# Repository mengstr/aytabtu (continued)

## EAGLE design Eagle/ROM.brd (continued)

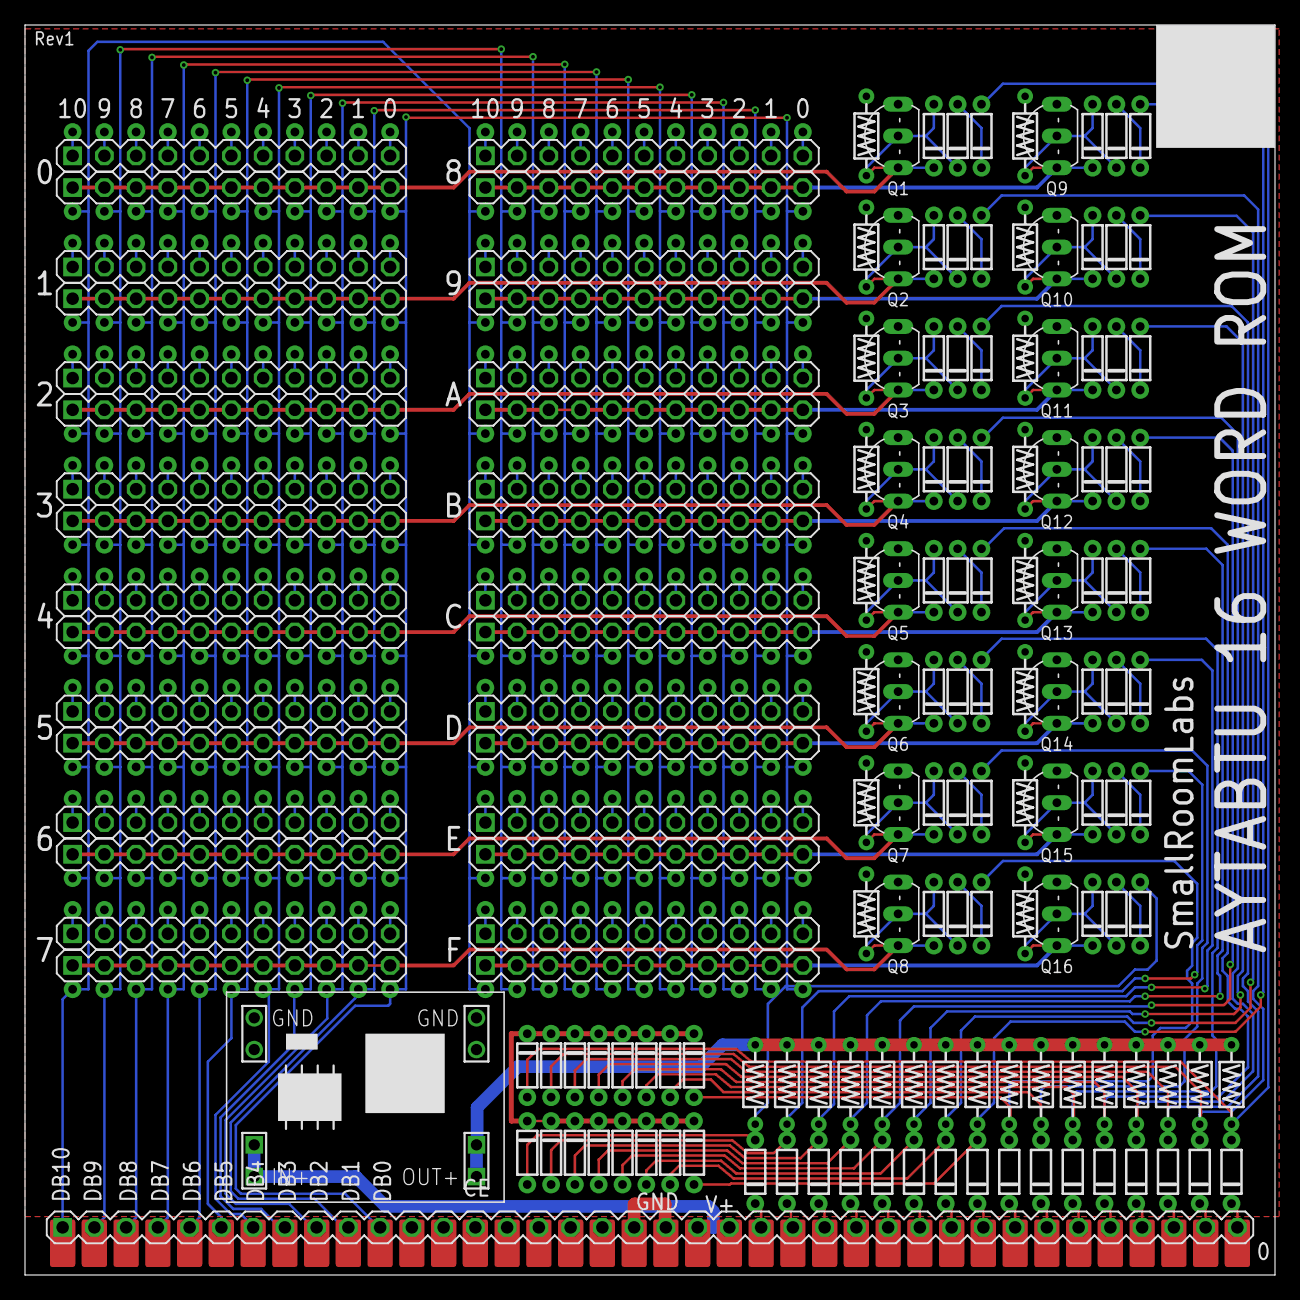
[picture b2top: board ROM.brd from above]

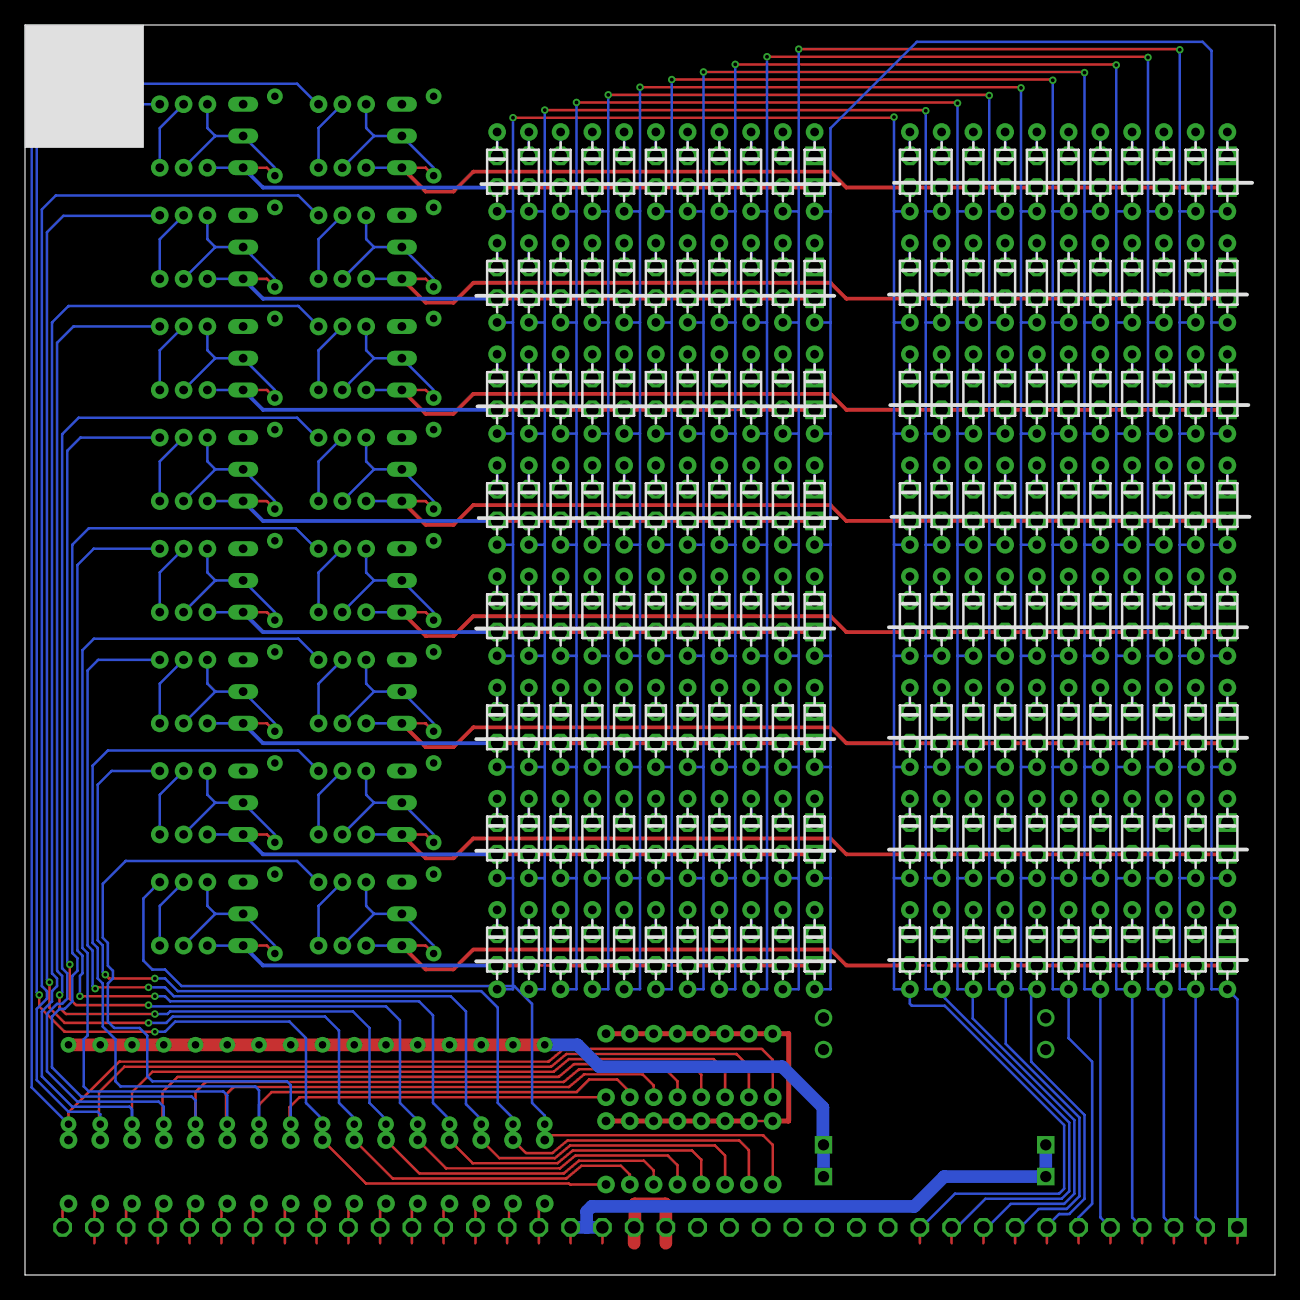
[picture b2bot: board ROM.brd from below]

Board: 2 copper layers, 100.0 x 100.0 mm, 338 parts (176 on the bottom side), 271 nets.

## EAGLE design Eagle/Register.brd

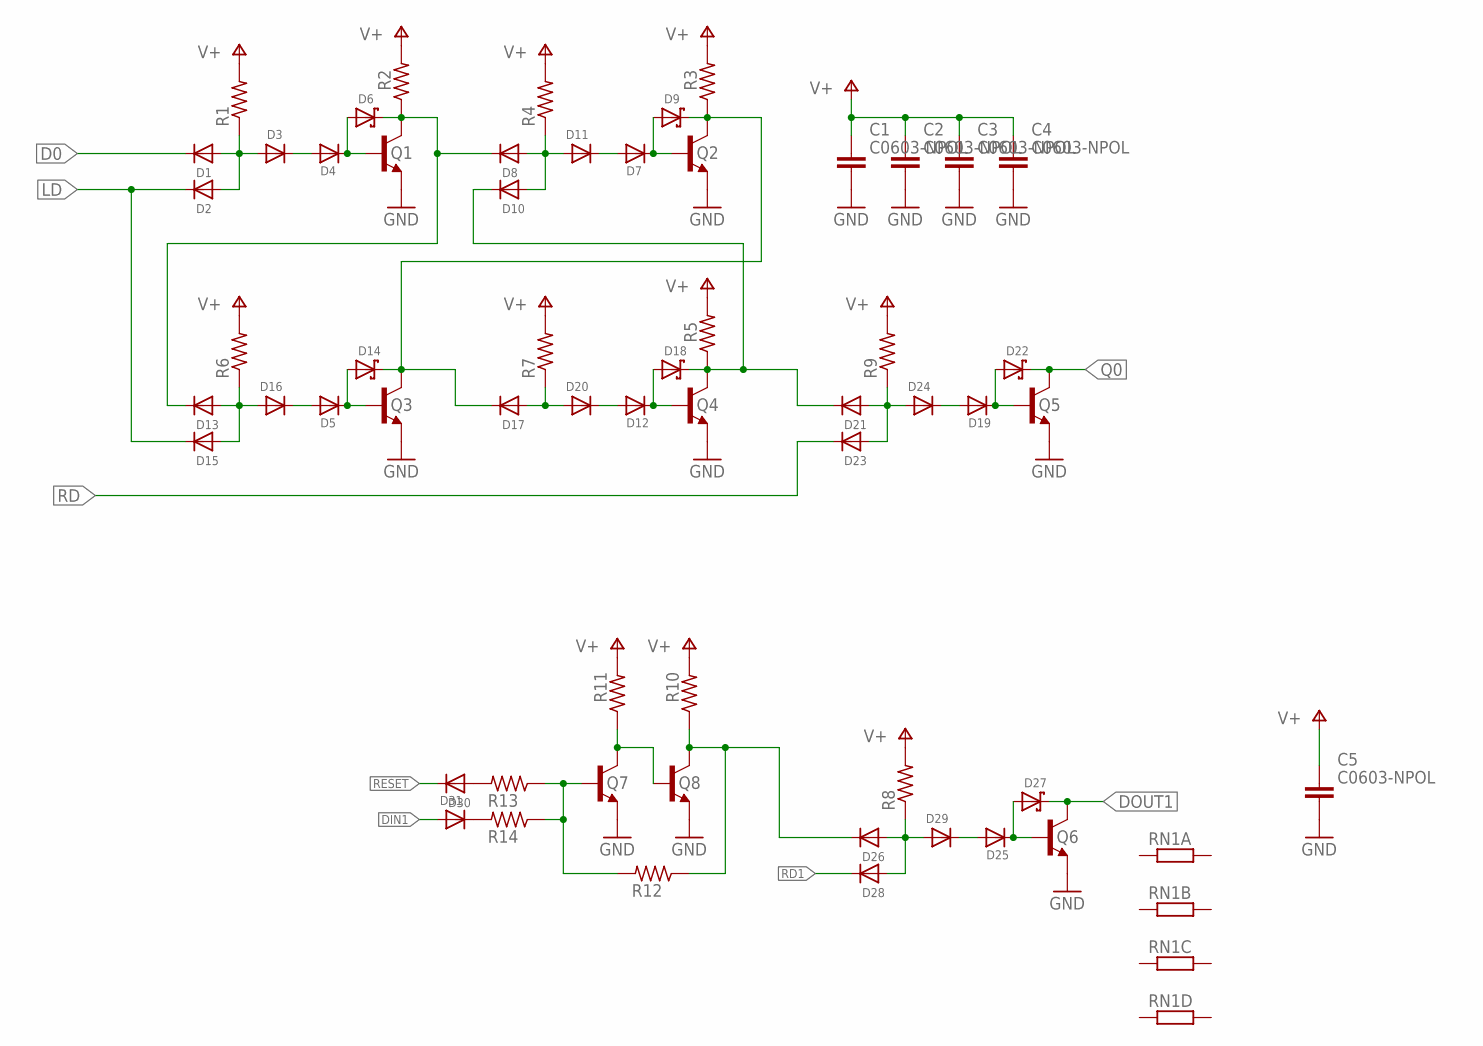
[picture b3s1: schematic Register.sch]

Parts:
C1, C2, C3, C4, C5: C0603-NPOL; C0603
D1, D2, D3, D4, D5, D7, D8, D10, D11, D12, D13, D15, D16, D17, D19, D20, D21, D23, D24, D25, D26, D28, D29, D30, D31: DIODE-SOD323; SOD323F
D6, D9, D14, D18, D22, D27: SCHOTTKYSOT323; SOT23
Q1, Q2, Q3, Q4, Q5, Q6, Q7, Q8: BC547-SOT23; SOT23
R1, R4, R6, R7, R8, R9: 470; R0805
R2, R3, R5, R10, R11, R12, R13, R14: 150; R0805
RN1: RESISTOR_ARRAY_4; RN8P-4R-CRA06S

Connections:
D0: D1.C
DIN1: D31.A
DOUT1: D27.3 (C), Q6.3 (C)
GND: C1.2, C2.2, C3.2, C4.2, C5.2, Q1.2 (E), Q2.2 (E), Q3.2 (E), Q4.2 (E), Q5.2 (E), Q6.2 (E), Q7.2 (E), Q8.2 (E)
LD: D2.C, D15.C
unnamed: D1.A, D2.A, D3.A, R1.1
unnamed: D3.C, D4.A
unnamed: D4.C, D6.1 (A), Q1.1 (B)
unnamed: D13.A, D15.A, D16.A, R6.1
unnamed: D8.A, D10.A, D11.A, R4.1
unnamed: D5.A, D16.C
unnamed: D7.A, D11.C
unnamed: D5.C, D14.1 (A), Q3.1 (B)
unnamed: D7.C, D9.1 (A), Q2.1 (B)
unnamed: D17.A, D20.A, R7.1
unnamed: D12.A, D20.C
unnamed: D12.C, D18.1 (A), Q4.1 (B)
unnamed: D21.A, D23.A, D24.A, R9.1
unnamed: D19.A, D24.C
unnamed: D19.C, D22.1 (A), Q5.1 (B)
unnamed: D26.C, Q8.3 (C), R10.1, R12.1
unnamed: D26.A, D28.A, D29.A, R8.1
unnamed: D25.A, D29.C
unnamed: D25.C, D27.1 (A), Q6.1 (B)
unnamed: Q7.3 (C), Q8.1 (B), R11.1
unnamed: Q7.1 (B), R12.2, R13.1, R14.1
unnamed: D30.A, R13.2
unnamed: D31.C, R14.2
unnamed: D10.C, D18.3 (C), D21.C, Q4.3 (C), R5.1
unnamed: D9.3 (C), D14.3 (C), D17.C, Q2.3 (C), Q3.3 (C), R3.1
unnamed: D6.3 (C), D8.C, D13.C, Q1.3 (C), R2.1
Q0: D22.3 (C), Q5.3 (C)
RD: D23.C
RD1: D28.C
RESET: D30.C
V+: C1.1, C2.1, C3.1, C4.1, C5.1, R1.2, R2.2, R3.2, R4.2, R5.2, R6.2, R7.2, R8.2, R9.2, R10.2, R11.2

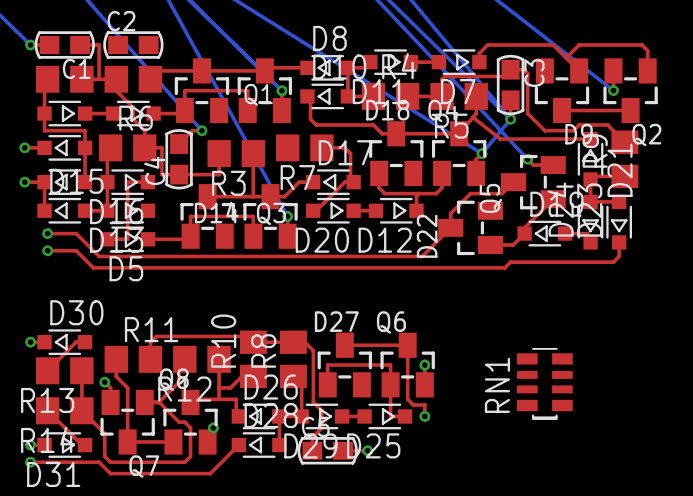
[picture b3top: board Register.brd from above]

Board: 2 copper layers, 59 parts (0 on the bottom side), 31 nets.

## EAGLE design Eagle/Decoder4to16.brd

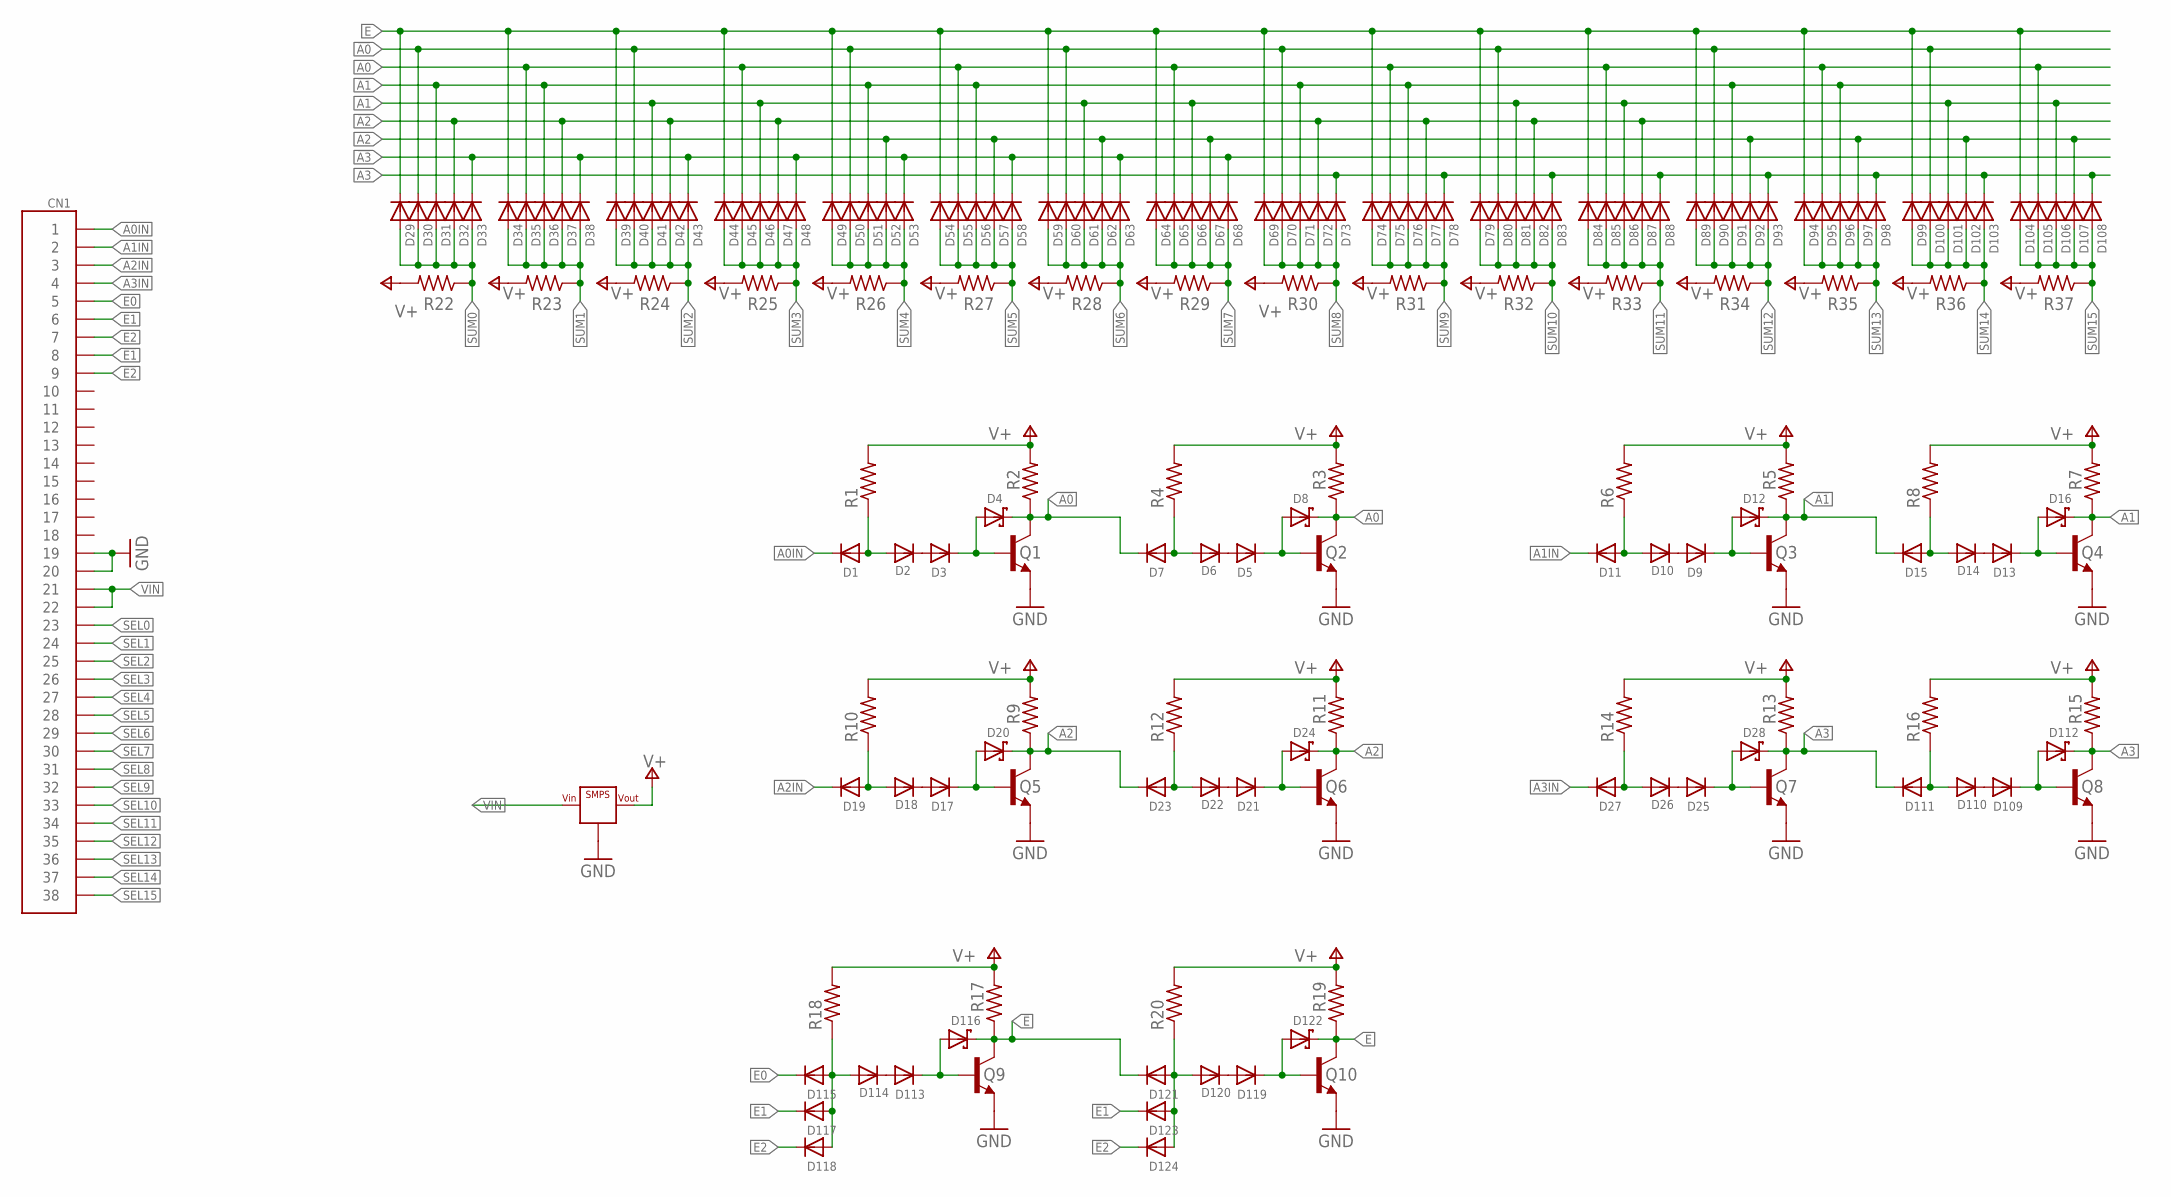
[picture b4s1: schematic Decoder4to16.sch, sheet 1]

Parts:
CN1: HD38-HP; HD38-HOLEPAD
D1, D2, D3, D5, D6, D7, D9, D10, D11, D13, D14, D15, D17, D18, D19, D21, D22, D23, D25, D26, D27, D29, D30, D31, D32, D33, D34, D35, D36, D37, D38, D39, D40, D41, D42, D43, D44, D45, D46, D47, D48, D49, D50, D51, D52, D53, D54, D55, D56, D57, D58, D59, D60, D61, D62, D63, D64, D65, D66, D67, D68, D69, D70, D71, D72, D73, D74, D75, D76, D77, D78, D79, D80, D81, D82, D83, D84, D85, D86, D87, D88, D89, D90, D91, D92, D93, D94, D95, D96, D97, D98, D99, D100, D101, D102, D103, D104, D105, D106, D107, D108, D109, D110, D111, D113, D114, D115, D117, D118, D119, D120, D121, D123, D124: DIODE-SOD323; SOD323F
D4, D8, D12, D16, D20, D24, D28, D112, D116, D122: SCHOTTKYSOT323; SOT23
Q1, Q2, Q3, Q4, Q5, Q6, Q7, Q8, Q9, Q10: BC547-SOT23; SOT23
R1, R4, R6, R8, R10, R12, R14, R16, R18, R20: 470; R0805
R2, R3, R5, R7, R9, R11, R13, R15, R17, R19: 150; R0805
R22, R23, R24, R25, R26, R27, R28, R29, R30, R31, R32, R33, R34, R35, R36, R37: R-0805; R0805
VR1: SMPS; BUCK1722

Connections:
!A0: D4.3 (C), D7.C, D30.C, D40.C, D50.C, D60.C, D70.C, D80.C, D90.C, D100.C, Q1.3 (C), R2.1
!A1: D12.3 (C), D15.C, D31.C, D36.C, D51.C, D56.C, D71.C, D76.C, D91.C, D96.C, Q3.3 (C), R5.1
!A2: D20.3 (C), D23.C, D32.C, D37.C, D42.C, D47.C, D72.C, D77.C, D82.C, D87.C, Q5.3 (C), R9.1
!A3: D28.3 (C), D33.C, D38.C, D43.C, D48.C, D53.C, D58.C, D63.C, D68.C, D111.C, Q7.3 (C), R13.1
!E: D116.3 (C), D121.C, Q9.3 (C), R17.1
!E1: CN1.P8@1 (8), CN1.P8@2 (8), D123.C
!E2: CN1.P9@1 (9), CN1.P9@2 (9), D124.C
A0: D8.3 (C), D35.C, D45.C, D55.C, D65.C, D75.C, D85.C, D95.C, D105.C, Q2.3 (C), R3.1
A0IN: CN1.P1@1 (1), CN1.P1@2 (1), D1.C
A1: D16.3 (C), D41.C, D46.C, D61.C, D66.C, D81.C, D86.C, D101.C, D106.C, Q4.3 (C), R7.1
A1IN: CN1.P2@1 (2), CN1.P2@2 (2), D11.C
A2: D24.3 (C), D52.C, D57.C, D62.C, D67.C, D92.C, D97.C, D102.C, D107.C, Q6.3 (C), R11.1
A2IN: CN1.P3@1 (3), CN1.P3@2 (3), D19.C
A3: D73.C, D78.C, D83.C, D88.C, D93.C, D98.C, D103.C, D108.C, D112.3 (C), Q8.3 (C), R15.1
A3IN: CN1.P4@1 (4), CN1.P4@2 (4), D27.C
E: D29.C, D34.C, D39.C, D44.C, D49.C, D54.C, D59.C, D64.C, D69.C, D74.C, D79.C, D84.C, D89.C, D94.C, D99.C, D104.C, D122.3 (C), Q10.3 (C), R19.1
E0: CN1.P5@1 (5), CN1.P5@2 (5), D115.C
E1: CN1.P6@1 (6), CN1.P6@2 (6), D117.C
E2: CN1.P7@1 (7), CN1.P7@2 (7), D118.C
GND: CN1.P19@1 (19), CN1.P19@2 (19), CN1.P20@1 (20), CN1.P20@2 (20), Q1.2 (E), Q2.2 (E), Q3.2 (E), Q4.2 (E), Q5.2 (E), Q6.2 (E), Q7.2 (E), Q8.2 (E), Q9.2 (E), Q10.2 (E), VR1.GND@1 (GND), VR1.GND@2 (GND), VR1.GND@3 (GND), VR1.GND@4 (GND); also elsewhere on the board
unnamed: D1.A, D2.A, R1.1
unnamed: D3.C, D4.1 (A), Q1.1 (B)
unnamed: D2.C, D3.A
unnamed: D5.C, D8.1 (A), Q2.1 (B)
unnamed: D5.A, D6.C
unnamed: D6.A, D7.A, R4.1
unnamed: D9.C, D12.1 (A), Q3.1 (B)
unnamed: D9.A, D10.C
unnamed: D10.A, D11.A, R6.1
unnamed: D13.C, D16.1 (A), Q4.1 (B)
unnamed: D13.A, D14.C
unnamed: D14.A, D15.A, R8.1
unnamed: D17.C, D20.1 (A), Q5.1 (B)
unnamed: D17.A, D18.C
unnamed: D18.A, D19.A, R10.1
unnamed: D21.C, D24.1 (A), Q6.1 (B)
unnamed: D21.A, D22.C
unnamed: D22.A, D23.A, R12.1
unnamed: D25.C, D28.1 (A), Q7.1 (B)
unnamed: D25.A, D26.C
unnamed: D26.A, D27.A, R14.1
unnamed: D109.C, D112.1 (A), Q8.1 (B)
unnamed: D109.A, D110.C
unnamed: D110.A, D111.A, R16.1
unnamed: D113.C, D116.1 (A), Q9.1 (B)
unnamed: D113.A, D114.C
unnamed: D119.C, D122.1 (A), Q10.1 (B)
unnamed: D119.A, D120.C
unnamed: D120.A, D121.A, D123.A, D124.A, R20.1
unnamed: D114.A, D115.A, D117.A, D118.A, R18.1
SEL0: CN1.P23@1 (23), CN1.P23@2 (23); also elsewhere on the board
SEL1: CN1.P24@1 (24), CN1.P24@2 (24); also elsewhere on the board
SEL2: CN1.P25@1 (25), CN1.P25@2 (25); also elsewhere on the board
SEL3: CN1.P26@1 (26), CN1.P26@2 (26); also elsewhere on the board
SEL4: CN1.P27@1 (27), CN1.P27@2 (27); also elsewhere on the board
SEL5: CN1.P28@1 (28), CN1.P28@2 (28); also elsewhere on the board
SEL6: CN1.P29@1 (29), CN1.P29@2 (29); also elsewhere on the board
SEL7: CN1.P30@1 (30), CN1.P30@2 (30); also elsewhere on the board
SEL8: CN1.P31@1 (31), CN1.P31@2 (31); also elsewhere on the board
SEL9: CN1.P32@1 (32), CN1.P32@2 (32); also elsewhere on the board
SEL10: CN1.P33@1 (33), CN1.P33@2 (33); also elsewhere on the board
SEL11: CN1.P34@1 (34), CN1.P34@2 (34); also elsewhere on the board
SEL12: CN1.P35@1 (35), CN1.P35@2 (35); also elsewhere on the board
SEL13: CN1.P36@1 (36), CN1.P36@2 (36); also elsewhere on the board
SEL14: CN1.P37@1 (37), CN1.P37@2 (37); also elsewhere on the board
SEL15: CN1.P38@1 (38), CN1.P38@2 (38); also elsewhere on the board
SUM0: D29.A, D30.A, D31.A, D32.A, D33.A, R22.1; also elsewhere on the board
SUM1: D34.A, D35.A, D36.A, D37.A, D38.A, R23.1; also elsewhere on the board
SUM2: D39.A, D40.A, D41.A, D42.A, D43.A, R24.1; also elsewhere on the board
SUM3: D44.A, D45.A, D46.A, D47.A, D48.A, R25.1; also elsewhere on the board
SUM4: D49.A, D50.A, D51.A, D52.A, D53.A, R26.1; also elsewhere on the board
SUM5: D54.A, D55.A, D56.A, D57.A, D58.A, R27.1; also elsewhere on the board
SUM6: D59.A, D60.A, D61.A, D62.A, D63.A, R28.1; also elsewhere on the board
SUM7: D64.A, D65.A, D66.A, D67.A, D68.A, R29.1; also elsewhere on the board
SUM8: D69.A, D70.A, D71.A, D72.A, D73.A, R30.1; also elsewhere on the board
SUM9: D74.A, D75.A, D76.A, D77.A, D78.A, R31.1; also elsewhere on the board
SUM10: D79.A, D80.A, D81.A, D82.A, D83.A, R32.1; also elsewhere on the board
SUM11: D84.A, D85.A, D86.A, D87.A, D88.A, R33.1; also elsewhere on the board
SUM12: D89.A, D90.A, D91.A, D92.A, D93.A, R34.1; also elsewhere on the board
SUM13: D94.A, D95.A, D96.A, D97.A, D98.A, R35.1; also elsewhere on the board
SUM14: D99.A, D100.A, D101.A, D102.A, D103.A, R36.1; also elsewhere on the board
SUM15: D104.A, D105.A, D106.A, D107.A, D108.A, R37.1; also elsewhere on the board
V+: R1.2, R2.2, R3.2, R4.2, R5.2, R6.2, R7.2, R8.2, R9.2, R10.2, R11.2, R12.2, R13.2, R14.2, R15.2, R16.2, R17.2, R18.2, R19.2, R20.2, R22.2, R23.2, R24.2, R25.2, R26.2, R27.2, R28.2, R29.2, R30.2, R31.2, R32.2, R33.2, R34.2, R35.2, R36.2, R37.2, VR1.OUT@1 (VOUT), VR1.OUT@2 (VOUT); also elsewhere on the board
VIN: CN1.P21@1 (21), CN1.P21@2 (21), CN1.P22@1 (22), CN1.P22@2 (22), VR1.IN@1 (VIN), VR1.IN@2 (VIN)

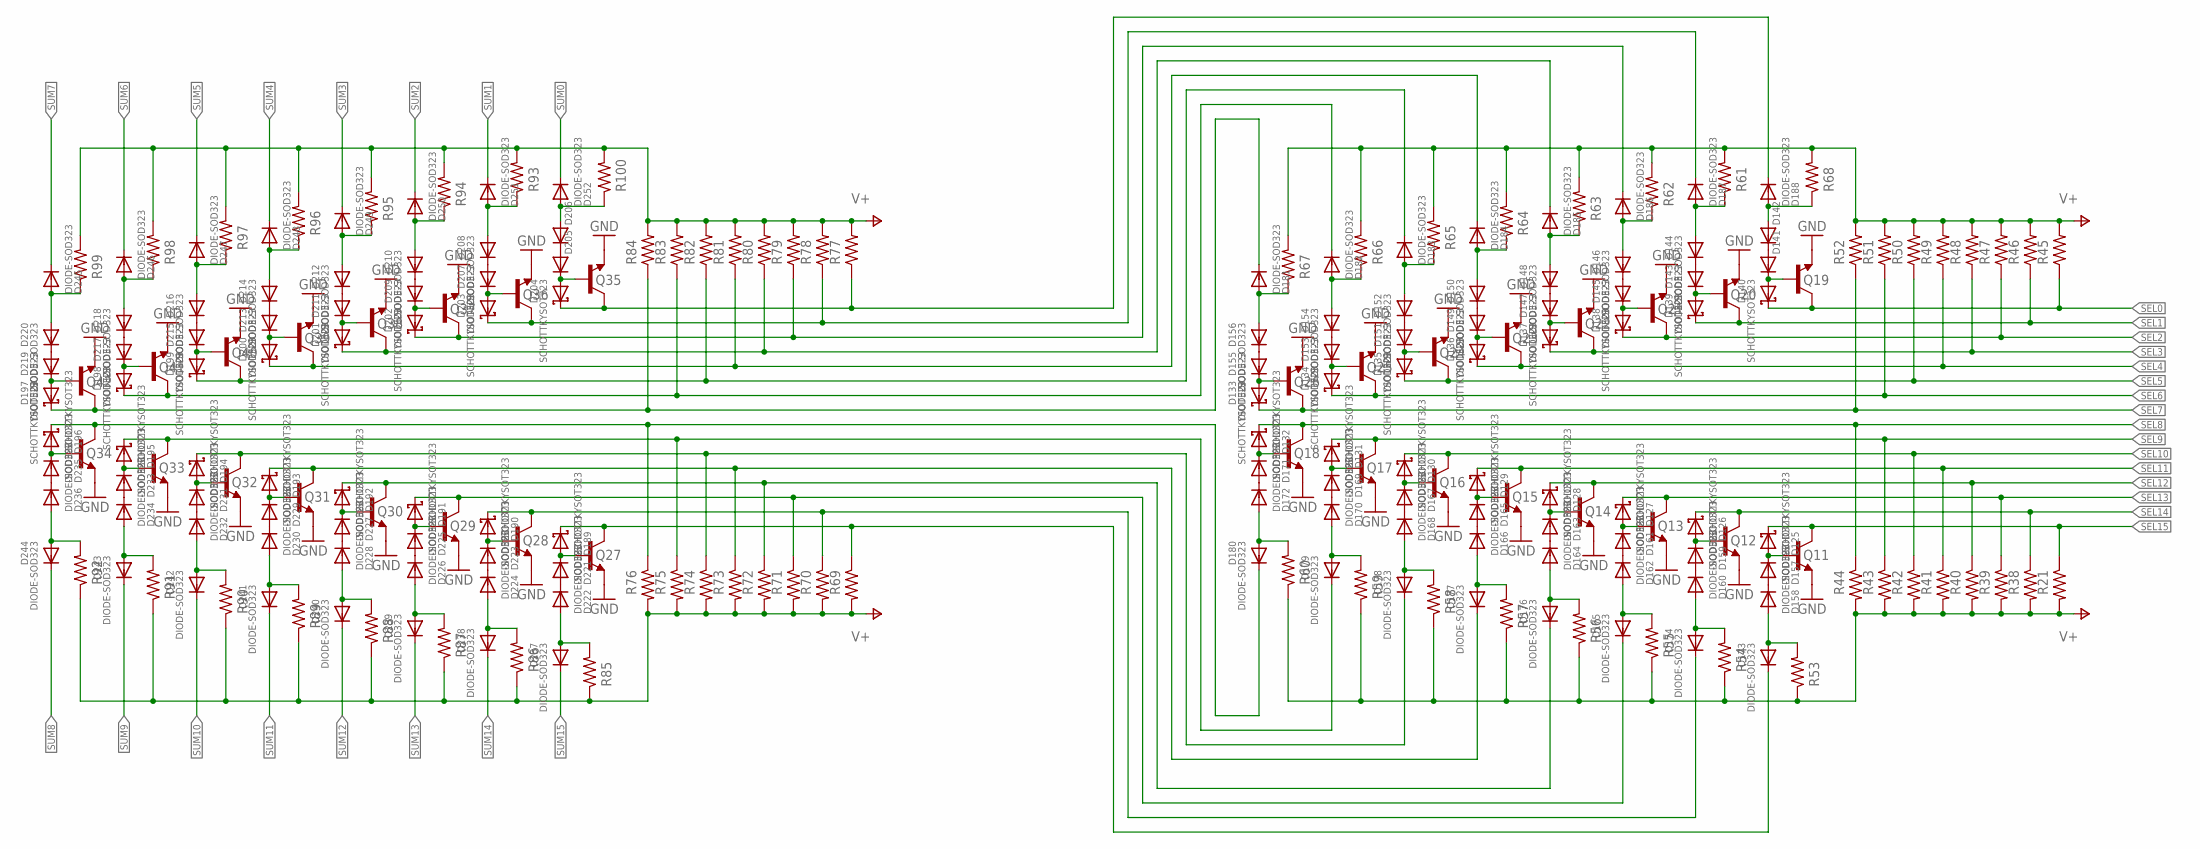
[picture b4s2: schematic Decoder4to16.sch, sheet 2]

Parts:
D125, D126, D127, D128, D129, D130, D131, D132, D133, D134, D135, D136, D137, D138, D139, D140, D189, D190, D191, D192, D193, D194, D195, D196, D197, D198, D199, D200, D201, D202, D203, D204: SCHOTTKYSOT323; SOT23
D141, D142, D143, D144, D145, D146, D147, D148, D149, D150, D151, D152, D153, D154, D155, D156, D157, D158, D159, D160, D161, D162, D163, D164, D165, D166, D167, D168, D169, D170, D171, D172, D173, D174, D175, D176, D177, D178, D179, D180, D181, D182, D183, D184, D185, D186, D187, D188, D205, D206, D207, D208, D209, D210, D211, D212, D213, D214, D215, D216, D217, D218, D219, D220, D221, D222, D223, D224, D225, D226, D227, D228, D229, D230, D231, D232, D233, D234, D235, D236, D237, D238, D239, D240, D241, D242, D243, D244, D245, D246, D247, D248, D249, D250, D251, D252: DIODE-SOD323; SOD323F
Q11, Q12, Q13, Q14, Q15, Q16, Q17, Q18, Q19, Q20, Q21, Q22, Q23, Q24, Q25, Q26, Q27, Q28, Q29, Q30, Q31, Q32, Q33, Q34, Q35, Q36, Q37, Q38, Q39, Q40, Q41, Q42: BC547-SOT23; SOT23
R21, R38, R39, R40, R41, R42, R43, R44, R45, R46, R47, R48, R49, R50, R51, R52, R53, R54, R55, R56, R57, R58, R59, R60, R61, R62, R63, R64, R65, R66, R67, R68, R69, R70, R71, R72, R73, R74, R75, R76, R77, R78, R79, R80, R81, R82, R83, R84, R85, R86, R87, R88, R89, R90, R91, R92, R93, R94, R95, R96, R97, R98, R99, R100: R-0805; R0805

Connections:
GND: Q11.2 (E), Q12.2 (E), Q13.2 (E), Q14.2 (E), Q15.2 (E), Q16.2 (E), Q17.2 (E), Q18.2 (E), Q19.2 (E), Q20.2 (E), Q21.2 (E), Q22.2 (E), Q23.2 (E), Q24.2 (E), Q25.2 (E), Q26.2 (E), Q27.2 (E), Q28.2 (E), Q29.2 (E), Q30.2 (E), Q31.2 (E), Q32.2 (E), Q33.2 (E), Q34.2 (E), Q35.2 (E), Q36.2 (E), Q37.2 (E), Q38.2 (E), Q39.2 (E), Q40.2 (E), Q41.2 (E), Q42.2 (E); also elsewhere on the board
unnamed: D125.1 (A), D157.C, Q11.1 (B)
unnamed: D126.1 (A), D159.C, Q12.1 (B)
unnamed: D127.1 (A), D161.C, Q13.1 (B)
unnamed: D128.1 (A), D163.C, Q14.1 (B)
unnamed: D129.1 (A), D165.C, Q15.1 (B)
unnamed: D130.1 (A), D167.C, Q16.1 (B)
unnamed: D131.1 (A), D169.C, Q17.1 (B)
unnamed: D132.1 (A), D171.C, Q18.1 (B)
unnamed: D140.1 (A), D141.C, Q19.1 (B)
unnamed: D139.1 (A), D143.C, Q20.1 (B)
unnamed: D138.1 (A), D145.C, Q21.1 (B)
unnamed: D137.1 (A), D147.C, Q22.1 (B)
unnamed: D136.1 (A), D149.C, Q23.1 (B)
unnamed: D135.1 (A), D151.C, Q24.1 (B)
unnamed: D134.1 (A), D153.C, Q25.1 (B)
unnamed: D133.1 (A), D155.C, Q26.1 (B)
unnamed: D141.A, D142.C
unnamed: D143.A, D144.C
unnamed: D145.A, D146.C
unnamed: D147.A, D148.C
unnamed: D149.A, D150.C
unnamed: D151.A, D152.C
unnamed: D153.A, D154.C
unnamed: D155.A, D156.C
unnamed: D157.A, D158.C
unnamed: D159.A, D160.C
unnamed: D161.A, D162.C
unnamed: D163.A, D164.C
unnamed: D165.A, D166.C
unnamed: D167.A, D168.C
unnamed: D169.A, D170.C
unnamed: D171.A, D172.C
unnamed: D158.A, D173.A, R53.2
unnamed: D160.A, D174.A, R54.2
unnamed: D162.A, D175.A, R55.2
unnamed: D164.A, D176.A, R56.2
unnamed: D166.A, D177.A, R57.2
unnamed: D168.A, D178.A, R58.2
unnamed: D170.A, D179.A, R59.2
unnamed: D172.A, D180.A, R60.2
unnamed: D156.A, D181.A, R67.1
unnamed: D154.A, D182.A, R66.1
unnamed: D152.A, D183.A, R65.1
unnamed: D150.A, D184.A, R64.1
unnamed: D148.A, D185.A, R63.1
unnamed: D146.A, D186.A, R62.1
unnamed: D144.A, D187.A, R61.1
unnamed: D142.A, D188.A, R68.1
unnamed: D189.1 (A), D221.C, Q27.1 (B)
unnamed: D190.1 (A), D223.C, Q28.1 (B)
unnamed: D191.1 (A), D225.C, Q29.1 (B)
unnamed: D192.1 (A), D227.C, Q30.1 (B)
unnamed: D193.1 (A), D229.C, Q31.1 (B)
unnamed: D194.1 (A), D231.C, Q32.1 (B)
unnamed: D195.1 (A), D233.C, Q33.1 (B)
unnamed: D196.1 (A), D235.C, Q34.1 (B)
unnamed: D204.1 (A), D205.C, Q35.1 (B)
unnamed: D203.1 (A), D207.C, Q36.1 (B)
unnamed: D202.1 (A), D209.C, Q37.1 (B)
unnamed: D201.1 (A), D211.C, Q38.1 (B)
unnamed: D200.1 (A), D213.C, Q39.1 (B)
unnamed: D199.1 (A), D215.C, Q40.1 (B)
unnamed: D198.1 (A), D217.C, Q41.1 (B)
unnamed: D197.1 (A), D219.C, Q42.1 (B)
unnamed: D205.A, D206.C
unnamed: D207.A, D208.C
unnamed: D209.A, D210.C
unnamed: D211.A, D212.C
unnamed: D213.A, D214.C
unnamed: D215.A, D216.C
unnamed: D217.A, D218.C
unnamed: D219.A, D220.C
unnamed: D221.A, D222.C
unnamed: D223.A, D224.C
unnamed: D225.A, D226.C
unnamed: D227.A, D228.C
unnamed: D229.A, D230.C
unnamed: D231.A, D232.C
unnamed: D233.A, D234.C
unnamed: D235.A, D236.C
unnamed: D222.A, D237.A, R85.2
unnamed: D224.A, D238.A, R86.2
unnamed: D226.A, D239.A, R87.2
unnamed: D228.A, D240.A, R88.2
unnamed: D230.A, D241.A, R89.2
unnamed: D232.A, D242.A, R90.2
unnamed: D234.A, D243.A, R91.2
unnamed: D236.A, D244.A, R92.2
unnamed: D220.A, D245.A, R99.1
unnamed: D218.A, D246.A, R98.1
unnamed: D216.A, D247.A, R97.1
unnamed: D214.A, D248.A, R96.1
unnamed: D212.A, D249.A, R95.1
unnamed: D210.A, D250.A, R94.1
unnamed: D208.A, D251.A, R93.1
unnamed: D206.A, D252.A, R100.1
SEL0: D140.3 (C), Q19.3 (C), R45.1; also elsewhere on the board
SEL1: D139.3 (C), Q20.3 (C), R46.1; also elsewhere on the board
SEL2: D138.3 (C), Q21.3 (C), R47.1; also elsewhere on the board
SEL3: D137.3 (C), Q22.3 (C), R48.1; also elsewhere on the board
SEL4: D136.3 (C), Q23.3 (C), R49.1; also elsewhere on the board
SEL5: D135.3 (C), Q24.3 (C), R50.1; also elsewhere on the board
SEL6: D134.3 (C), Q25.3 (C), R51.1; also elsewhere on the board
SEL7: D133.3 (C), Q26.3 (C), R52.1; also elsewhere on the board
SEL8: D132.3 (C), Q18.3 (C), R44.1; also elsewhere on the board
SEL9: D131.3 (C), Q17.3 (C), R43.1; also elsewhere on the board
SEL10: D130.3 (C), Q16.3 (C), R42.1; also elsewhere on the board
SEL11: D129.3 (C), Q15.3 (C), R41.1; also elsewhere on the board
SEL12: D128.3 (C), Q14.3 (C), R40.1; also elsewhere on the board
SEL13: D127.3 (C), Q13.3 (C), R39.1; also elsewhere on the board
SEL14: D126.3 (C), Q12.3 (C), R38.1; also elsewhere on the board
SEL15: D125.3 (C), Q11.3 (C), R21.1; also elsewhere on the board
SUM0: D252.C; also elsewhere on the board
SUM1: D251.C; also elsewhere on the board
SUM2: D250.C; also elsewhere on the board
SUM3: D249.C; also elsewhere on the board
SUM4: D248.C; also elsewhere on the board
SUM5: D247.C; also elsewhere on the board
SUM6: D246.C; also elsewhere on the board
SUM7: D245.C; also elsewhere on the board
SUM8: D244.C; also elsewhere on the board
SUM9: D243.C; also elsewhere on the board
SUM10: D242.C; also elsewhere on the board
SUM11: D241.C; also elsewhere on the board
SUM12: D240.C; also elsewhere on the board
SUM13: D239.C; also elsewhere on the board
SUM14: D238.C; also elsewhere on the board
SUM15: D237.C; also elsewhere on the board
V+: R21.2, R38.2, R39.2, R40.2, R41.2, R42.2, R43.2, R44.2, R45.2, R46.2, R47.2, R48.2, R49.2, R50.2, R51.2, R52.2, R53.1, R54.1, R55.1, R56.1, R57.1, R58.1, R59.1, R60.1, R61.2, R62.2, R63.2, R64.2, R65.2, R66.2, R67.2, R68.2, R69.2, R70.2, R71.2, R72.2, R73.2, R74.2, R75.2, R76.2, R77.2, R78.2, R79.2, R80.2, R81.2, R82.2, R83.2, R84.2, R85.1, R86.1, R87.1, R88.1, R89.1, R90.1, R91.1, R92.1, R93.2, R94.2, R95.2, R96.2, R97.2, R98.2, R99.2, R100.2; also elsewhere on the board
Z0: D188.C, D204.3 (C), Q35.3 (C), R77.1
Z1: D187.C, D203.3 (C), Q36.3 (C), R78.1
Z2: D186.C, D202.3 (C), Q37.3 (C), R79.1
Z3: D185.C, D201.3 (C), Q38.3 (C), R80.1
Z4: D184.C, D200.3 (C), Q39.3 (C), R81.1
Z5: D183.C, D199.3 (C), Q40.3 (C), R82.1
Z6: D182.C, D198.3 (C), Q41.3 (C), R83.1
Z7: D181.C, D197.3 (C), Q42.3 (C), R84.1
Z8: D180.C, D196.3 (C), Q34.3 (C), R76.1
Z9: D179.C, D195.3 (C), Q33.3 (C), R75.1
Z10: D178.C, D194.3 (C), Q32.3 (C), R74.1
Z11: D177.C, D193.3 (C), Q31.3 (C), R73.1
Z12: D176.C, D192.3 (C), Q30.3 (C), R72.1
Z13: D175.C, D191.3 (C), Q29.3 (C), R71.1
Z14: D174.C, D190.3 (C), Q28.3 (C), R70.1
Z15: D173.C, D189.3 (C), Q27.3 (C), R69.1

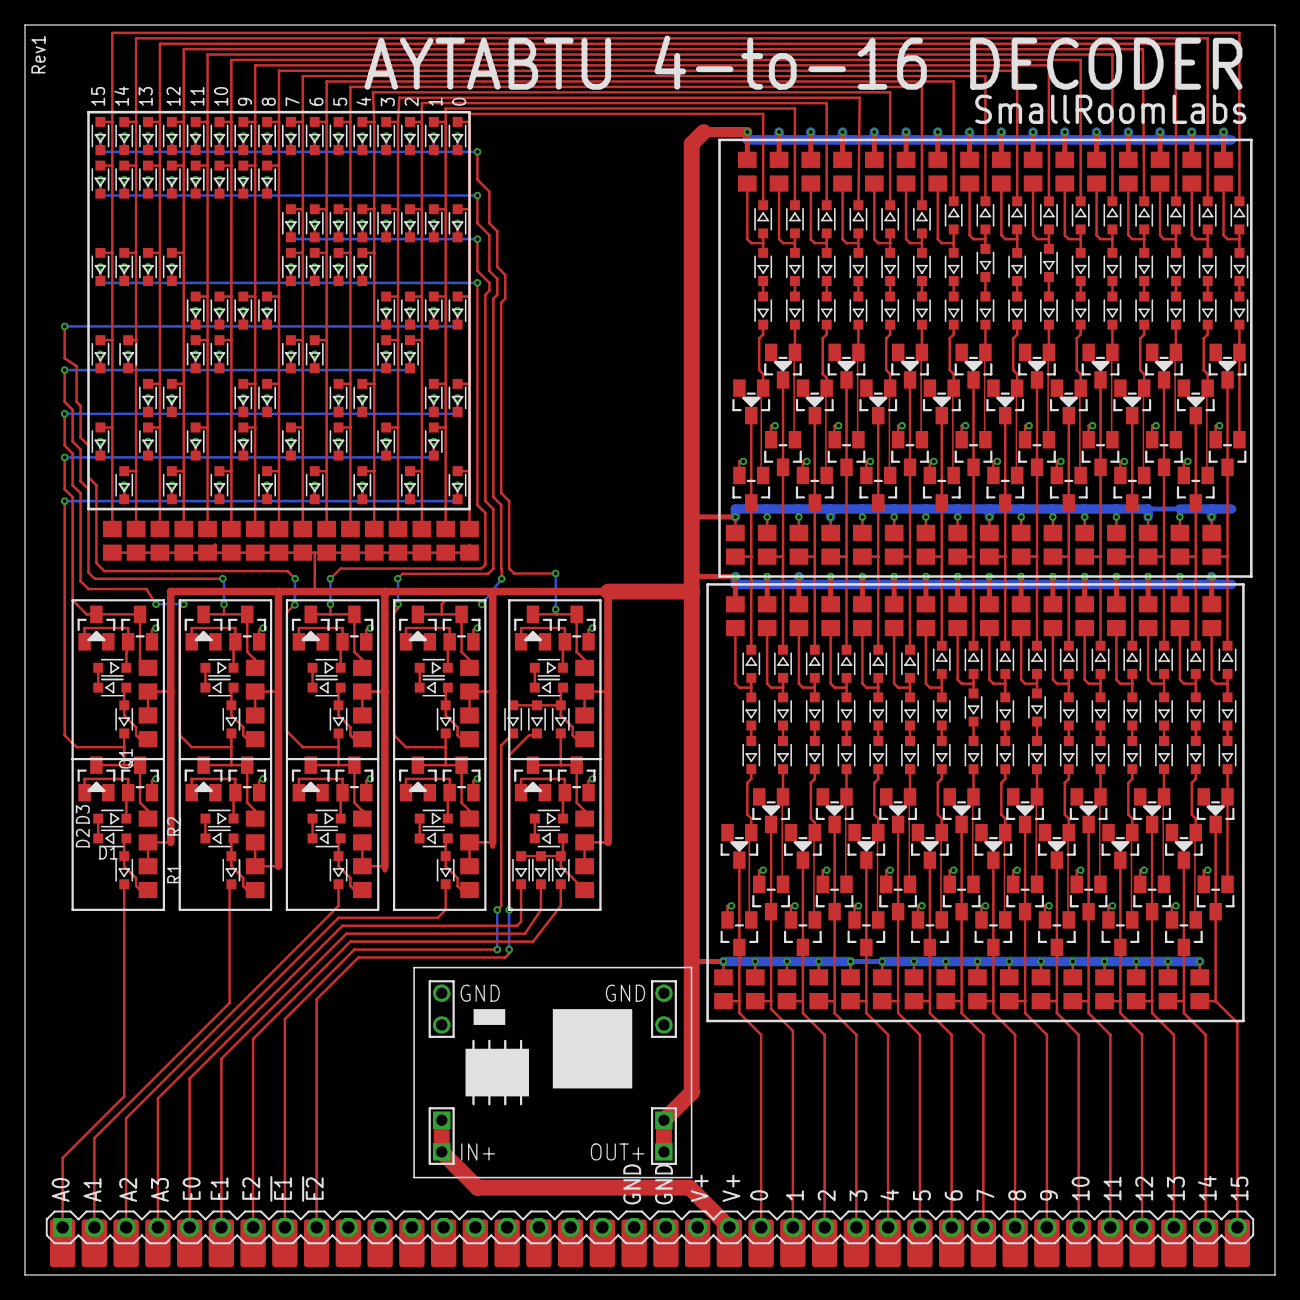
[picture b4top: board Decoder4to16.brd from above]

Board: 2 copper layers, 100.0 x 100.0 mm, 396 parts (0 on the bottom side), 196 nets.

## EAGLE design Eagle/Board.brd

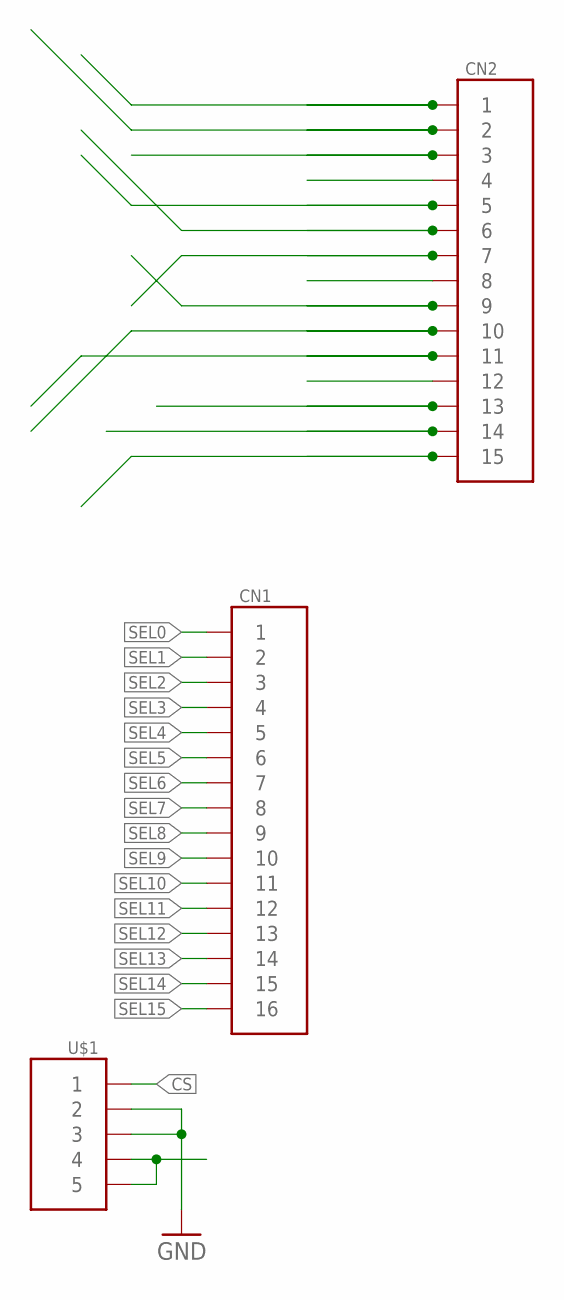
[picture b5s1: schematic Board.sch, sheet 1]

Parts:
CN1: HD16
CN2: HD15
U$1: HD5CN; HD5

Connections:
CS: U$1.P$1 (1)
GND: U$1.P$2 (2), U$1.P$3 (3); also elsewhere on the board
unnamed: U$1.P$4 (4), U$1.P$5 (5)
OUT0: CN2.P$1 (1)
OUT1: CN2.P$2 (2)
OUT2: CN2.P$3 (3)
OUT3: CN2.P$4 (4)
OUT4: CN2.P$5 (5)
OUT5: CN2.P$6 (6)
OUT6: CN2.P$7 (7)
OUT7: CN2.P$8 (8)
OUT8: CN2.P$9 (9)
OUT9: CN2.P$10 (10)
OUT10: CN2.P$11 (11)
OUT11: CN2.P$12 (12)
OUT12: CN2.P$13 (13)
OUT13: CN2.P$14 (14)
OUT14: CN2.P$15 (15)
SEL0: CN1.P$1 (1)
SEL1: CN1.P$2 (2)
SEL2: CN1.P$3 (3)
SEL3: CN1.P$4 (4)
SEL4: CN1.P$5 (5)
SEL5: CN1.P$6 (6)
SEL6: CN1.P$7 (7)
SEL7: CN1.P$8 (8)
SEL8: CN1.P$9 (9)
SEL9: CN1.P$10 (10)
SEL10: CN1.P$11 (11)
SEL11: CN1.P$12 (12)
SEL12: CN1.P$13 (13)
SEL13: CN1.P$14 (14)
SEL14: CN1.P$15 (15)
SEL15: CN1.P$16 (16)

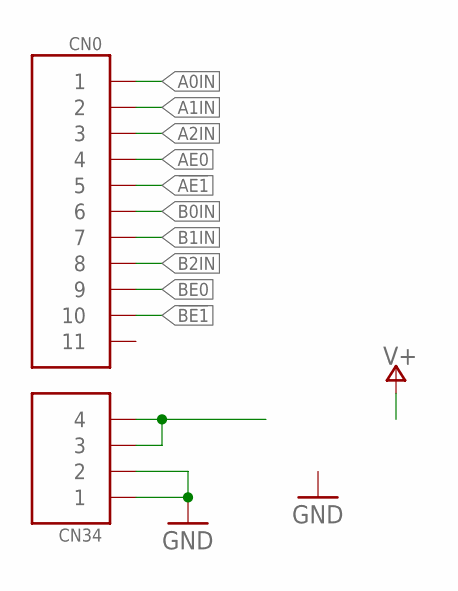
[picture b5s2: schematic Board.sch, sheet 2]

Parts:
CN0: HD11
CN34: HD4

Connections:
!AE1: CN0.P$5 (5)
!BE1: CN0.P$10 (10)
A0IN: CN0.P$1 (1); also elsewhere on the board
A1IN: CN0.P$2 (2); also elsewhere on the board
A2IN: CN0.P$3 (3); also elsewhere on the board
AE0: CN0.P$4 (4)
B0IN: CN0.P$6 (6)
B1IN: CN0.P$7 (7)
B2IN: CN0.P$8 (8)
BE0: CN0.P$9 (9)
GND: CN34.P$1 (1), CN34.P$2 (2); also elsewhere on the board
unnamed: CN34.P$3 (3), CN34.P$4 (4)

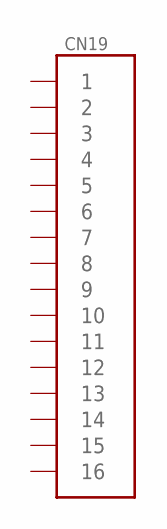
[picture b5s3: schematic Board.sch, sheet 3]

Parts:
CN19: HD16
